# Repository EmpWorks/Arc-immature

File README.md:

Arc60 solder pcb with 7u bottom.
Untested so use it at your own discretion.
update- forgot to add split 1.75u l shift key in kicad... will do it soon

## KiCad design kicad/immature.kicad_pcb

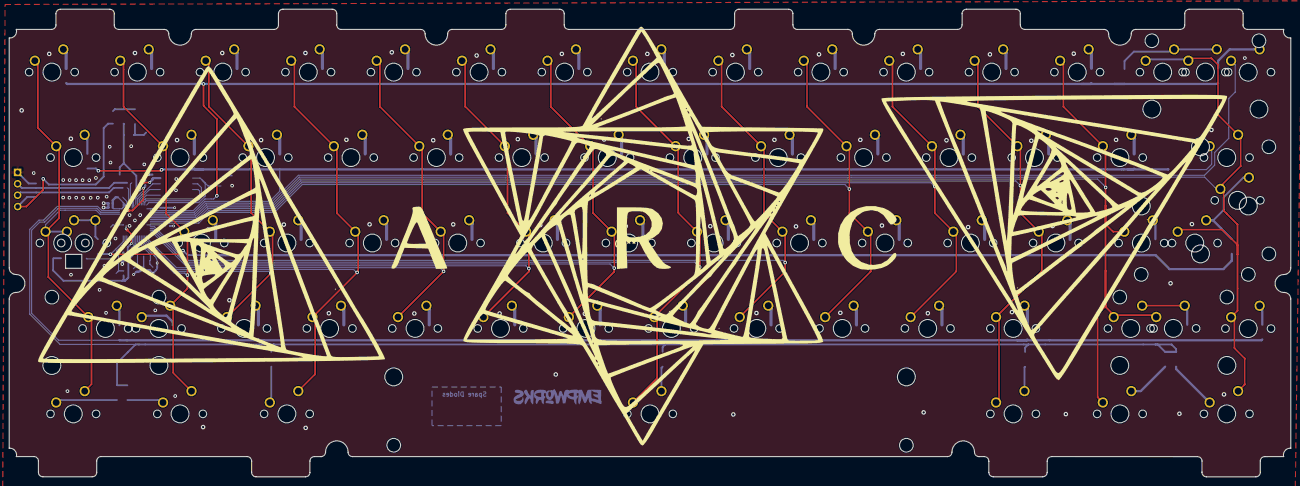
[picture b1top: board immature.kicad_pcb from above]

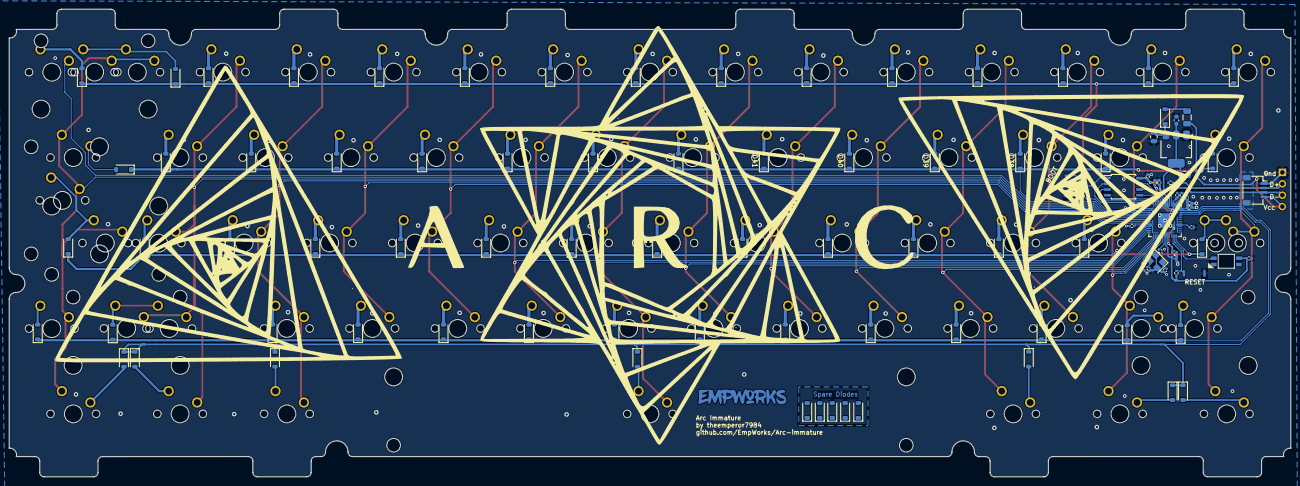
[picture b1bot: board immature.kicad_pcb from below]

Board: 2 copper layers, 285.7 x 104.3 mm, 171 parts (103 on the bottom side), 106 nets.

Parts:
BOOT: SW_DPST_x2; SW_SPST_CK_KXT3
C1, C5: 1uF; C_0402_1005Metric
C2, C3, C6, C7, C8, C9, C10, C11, C12, C17: 100nF; C_0402_1005Metric
C4: 10uF; C_0603_1608Metric
C13, C14: 22u; C_0805_2012Metric
C15, C16: 22pF; C_0402_1005Metric
C18: 100nf; C_0402_1005Metric
D1, D2, D3, D4, D18, D19, D20, D21, D22, D23, D24, D25, D26, D27, D28, D29, D30, D31, D36, D37, D38, D39, D40, D41, D42, D43, D44, D45, D46, D47, D48, D49, D53, D54, D55, D56, D57, D58, D59, D60, D61, D62, D63, D64, D65, D66, D68, D69, D70, D71, D72, D73, D74, D75, D75#2, D75#3, D75#4, D75#5, D75#6, D76, D77, D78, D81, D82, D83, D84, D86, D87, D88: D; D_SOD-123
D6: 1N4148W; D_SOD-123
F1: 500mA; Fuse_1206_3216Metric
J3: JST-SH-4P; JST_SH_SM04B-SRSS-TB_1x04-1MP_P1.00mm_Horizontal
J5: Conn_01x04; PinSocket_1x04_P2.54mm_Vertical
R1: 10k; R_0402_1005Metric
R2, R3: 27R; R_0402_1005Metric
R4, R5: 1k; R_0402_1005Metric
RESET: SW_DPST_x2; SW_SPST_CK_KXT3
SW1, SW4, SW18, SW19, SW20, SW21, SW22, SW23, SW24, SW25, SW26, SW27, SW28, SW29, SW30, SW38, SW39, SW40, SW41, SW42, SW43, SW44, SW45, SW46, SW47, SW48, SW49, SW57, SW58, SW59, SW60, SW61, SW62, SW63, SW64, SW65, SW66, SW67, SW73, SW74, SW75, SW76, SW77, SW78, SW79, SW80, SW81, SW82, SW90, SW98: ?; MX-Solderable-1U
SW5, SW55: ?; MX-Solderable-1.75U
SW6: fn; MX-Solderable-1U
SW7: iso; MX-Solderable-1U
SW8: lshift; MX-Solderable-1U
SW9: stpcaps; MX-Solderable-1.25U
SW10: iso; MX-Solderable-ISO
SW32: ?; MX-Solderable-2U
SW37, SW50, SW88, SW92, SW96, SW100: ?; MX-Solderable-1.5U
SW69: ?; MX-Solderable-2.25U-ReversedStabilizers
SW71: ?; MX-Solderable-2.25U
SW84: ?; MX-Solderable-2.75U
SW93: ?; MX-Solderable-7U-ReversedStabilizers
U1: AMS1117-3.3; SOT-223-3_TabPin2
U2: RP2040; QFN-56-1EP_7x7mm_P0.4mm_EP3.2x3.2mm
U4: W25Q128JVS; SOIC-8_5.23x5.23mm_P1.27mm
Y1: 12MHz; Crystal_SMD_3225-4Pin_3.2x2.5mm
rLED9: YS-SK6812MINI-E

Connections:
+1V1: C1.1, C2.1, C3.1, U2.23 (DVDD), U2.45 (VREG_VOUT), U2.50 (DVDD)
+3V3: C4.1, C5.1, C6.1, C7.1, C8.1, C9.1, C10.1, C11.1, C12.1, C14.1, C17.1, C18.1, R1.1, U1.2 (VO), U2.1 (IOVDD), U2.10 (IOVDD), U2.22 (IOVDD), U2.33 (IOVDD), U2.42 (IOVDD), U2.43 (ADC_AVDD), U2.44 (VREG_VIN), U2.48 (USB_VDD), U2.49 (IOVDD), U4.8 (VCC), rLED9.1 (VDD)
+5V: C13.1, D6.1 (K), U1.3 (VI)
/D_+: R2.2, U2.47 (D+)
/D_-: R3.2, U2.46 (D-)
/XTAL_O: C16.2, R4.1, Y1.1
/~USB_BOOT: BOOT.2 (B), R5.1
COL0: SW9.1, SW18.1, SW37.1, SW55.1, SW71.1, SW88.2, U2.39 (GPIO27/ADC1)
COL1: SW8.2, SW19.1, SW38.1, SW57.1, SW90.2, U2.18 (GPIO15)
COL2: SW20.1, SW39.1, SW58.1, SW73.1, U2.17 (GPIO14)
COL3: SW21.1, SW40.1, SW59.1, SW74.1, SW92.2, U2.16 (GPIO13)
COL4: SW22.1, SW41.1, SW60.1, SW75.1, U2.15 (GPIO12)
COL5: SW23.1, SW42.1, SW61.1, SW76.1, U2.14 (GPIO11)
COL6: SW24.1, SW43.1, SW62.1, SW77.1, U2.13 (GPIO10)
COL7: SW25.1, SW44.1, SW63.1, SW78.1, SW93.1, U2.12 (GPIO9)
COL8: SW26.1, SW45.1, SW64.1, SW79.1, U2.11 (GPIO8)
COL9: SW27.1, SW46.1, SW65.1, SW80.1, U2.9 (GPIO7)
COL10: SW28.1, SW47.1, SW66.1, SW81.1, U2.8 (GPIO6)
COL11: SW29.1, SW48.1, SW67.1, SW82.1, SW96.1, U2.7 (GPIO5)
COL12: SW5.1, SW7.1, SW30.1, SW49.1, SW84.1, SW98.1, U2.6 (GPIO4)
COL13: SW1.1, SW6.1, SW10.1, SW32.1, SW50.2, SW69.1, SW100.2, U2.5 (GPIO3)
COL14: SW4.1, U2.4 (GPIO2)
CS: R5.2, U2.56 (QSPI_SS_N), U4.1 (~CS)
DMINUS: J3.3, J5.3, R3.1
DPLUS: J3.2, J5.2, R2.1
GND: BOOT.1 (A), C1.2, C2.2, C3.2, C4.2, C5.2, C6.2, C7.2, C8.2, C9.2, C10.2, C11.2, C12.2, C13.2, C14.2, C15.1, C16.1, C17.2, C18.2, J3.1, J5.1, RESET.1 (A), U1.1 (GND), U2.19 (TESTEN), U2.57 (GND), U4.4 (GND), Y1.2, Y1.4, rLED9.3 (VSS)
LED_D: U2.27 (GPIO16), rLED9.4 (DIN)
unnamed: D1.2 (A), SW4.2
unnamed: D2.2 (A), SW6.2
unnamed: D3.2 (A), SW7.2
unnamed: D4.2 (A), SW8.1
unnamed: D6.2 (A), F1.2
unnamed: D18.2 (A), SW18.2
unnamed: D19.2 (A), SW19.2
unnamed: D20.2 (A), SW20.2
unnamed: D21.2 (A), SW21.2
unnamed: D22.2 (A), SW22.2
unnamed: D23.2 (A), SW23.2
unnamed: D24.2 (A), SW24.2
unnamed: D25.2 (A), SW25.2
unnamed: D26.2 (A), SW26.2
unnamed: D27.2 (A), SW27.2
unnamed: D28.2 (A), SW28.2
unnamed: D29.2 (A), SW29.2
unnamed: D30.2 (A), SW30.2
unnamed: D31.2 (A), SW1.2, SW32.2
unnamed: D36.2 (A), SW37.2
unnamed: D37.2 (A), SW38.2
unnamed: D38.2 (A), SW39.2
unnamed: D39.2 (A), SW40.2
unnamed: D40.2 (A), SW41.2
unnamed: D41.2 (A), SW42.2
unnamed: D42.2 (A), SW43.2
unnamed: D43.2 (A), SW44.2
unnamed: D44.2 (A), SW45.2
unnamed: D45.2 (A), SW46.2
unnamed: D46.2 (A), SW47.2
unnamed: D47.2 (A), SW48.2
unnamed: D48.2 (A), SW49.2
unnamed: D49.2 (A), SW50.1
unnamed: D53.2 (A), SW9.2, SW55.2
unnamed: D54.2 (A), SW57.2
unnamed: D55.2 (A), SW58.2
unnamed: D56.2 (A), SW59.2
unnamed: D57.2 (A), SW60.2
unnamed: D58.2 (A), SW61.2
unnamed: D59.2 (A), SW62.2
unnamed: D60.2 (A), SW63.2
unnamed: D61.2 (A), SW64.2
unnamed: D62.2 (A), SW65.2
unnamed: D63.2 (A), SW66.2
unnamed: D64.2 (A), SW67.2
unnamed: D65.2 (A), SW10.2, SW69.2
unnamed: D66.2 (A), SW71.2
unnamed: D68.2 (A), SW73.2
unnamed: D69.2 (A), SW74.2
unnamed: D70.2 (A), SW75.2
unnamed: D71.2 (A), SW76.2
unnamed: D72.2 (A), SW77.2
unnamed: D73.2 (A), SW78.2
unnamed: D74.2 (A), SW79.2
unnamed: D75.2 (A), D75#2.2 (A), D75#3.2 (A), D75#4.2 (A), D75#5.2 (A), D75#6.2 (A), SW80.2
unnamed: D76.2 (A), SW81.2
unnamed: D77.2 (A), SW82.2
unnamed: D78.2 (A), SW5.2, SW84.2
unnamed: D81.2 (A), SW88.1
unnamed: D82.2 (A), SW90.1
unnamed: D83.2 (A), SW92.1
unnamed: D84.2 (A), SW93.2
unnamed: D86.2 (A), SW96.2
unnamed: D87.2 (A), SW98.2
unnamed: D88.2 (A), SW100.1
unnamed: F1.1, J3.4, J5.4
QSPI_CLK: U2.52 (QSPI_SCLK), U4.6 (CLK)
ROW1: D1.1 (K), D18.1 (K), D19.1 (K), D20.1 (K), D21.1 (K), D22.1 (K), D23.1 (K), D24.1 (K), D25.1 (K), D26.1 (K), D27.1 (K), D28.1 (K), D29.1 (K), D30.1 (K), D31.1 (K), U2.2 (GPIO0)
ROW2: D36.1 (K), D37.1 (K), D38.1 (K), D39.1 (K), D40.1 (K), D41.1 (K), D42.1 (K), D43.1 (K), D44.1 (K), D45.1 (K), D46.1 (K), D47.1 (K), D48.1 (K), D49.1 (K), U2.3 (GPIO1)
ROW3: D3.1 (K), D53.1 (K), D54.1 (K), D55.1 (K), D56.1 (K), D57.1 (K), D58.1 (K), D59.1 (K), D60.1 (K), D61.1 (K), D62.1 (K), D63.1 (K), D64.1 (K), D65.1 (K), U2.28 (GPIO17)
ROW4: D2.1 (K), D4.1 (K), D66.1 (K), D68.1 (K), D69.1 (K), D70.1 (K), D71.1 (K), D72.1 (K), D73.1 (K), D74.1 (K), D75.1 (K), D75#2.1 (K), D75#3.1 (K), D75#4.1 (K), D75#5.1 (K), D75#6.1 (K), D76.1 (K), D77.1 (K), D78.1 (K), U2.40 (GPIO28/ADC2)
ROW5: D81.1 (K), D82.1 (K), D83.1 (K), D84.1 (K), D86.1 (K), D87.1 (K), D88.1 (K), U2.41 (GPIO29/ADC3)
SD0: U2.53 (QSPI_SD0), U4.5 (DI(IO0))
SD1: U2.55 (QSPI_SD1), U4.2 (DO(IO1))
SD2: U2.54 (QSPI_SD2), U4.3 (IO2)
SD3: U2.51 (QSPI_SD3), U4.7 (IO3)
XTAL_IN: C15.2, U2.20 (XTAL_IN), Y1.3
XTAL_OUT: R4.2, U2.21 (XTAL_OUT)
~RESET: R1.2, RESET.2 (B), U2.26 (~RUN)
